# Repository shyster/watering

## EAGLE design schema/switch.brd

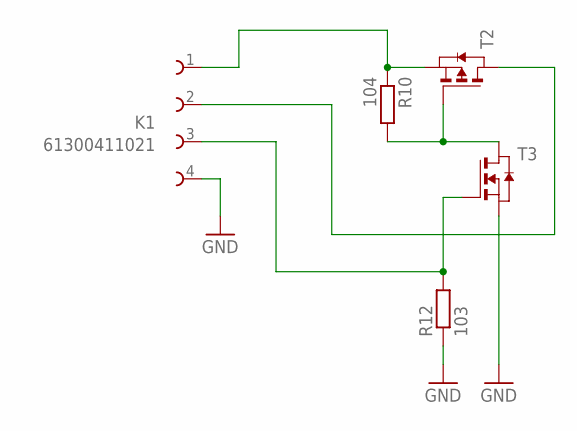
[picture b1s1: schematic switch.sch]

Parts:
K1: 61300411021
R10: 104; R0603
R12: 103; R0603
T2: PMOSSOT23; SOT-23
T3: NMOSSOT23; SOT-23

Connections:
GND: K1.4, R12.1, T3.2 (S)
unnamed: K1.2, T2.1 (D)
unnamed: R10.2, T2.3 (G), T3.1 (D)
unnamed: K1.3, R12.2, T3.3 (G)
unnamed: K1.1, R10.1, T2.2 (S)

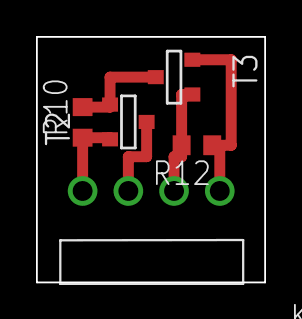
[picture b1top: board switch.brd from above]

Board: 2 copper layers, 12.7 x 13.6 mm, 5 parts (0 on the bottom side), 5 nets.

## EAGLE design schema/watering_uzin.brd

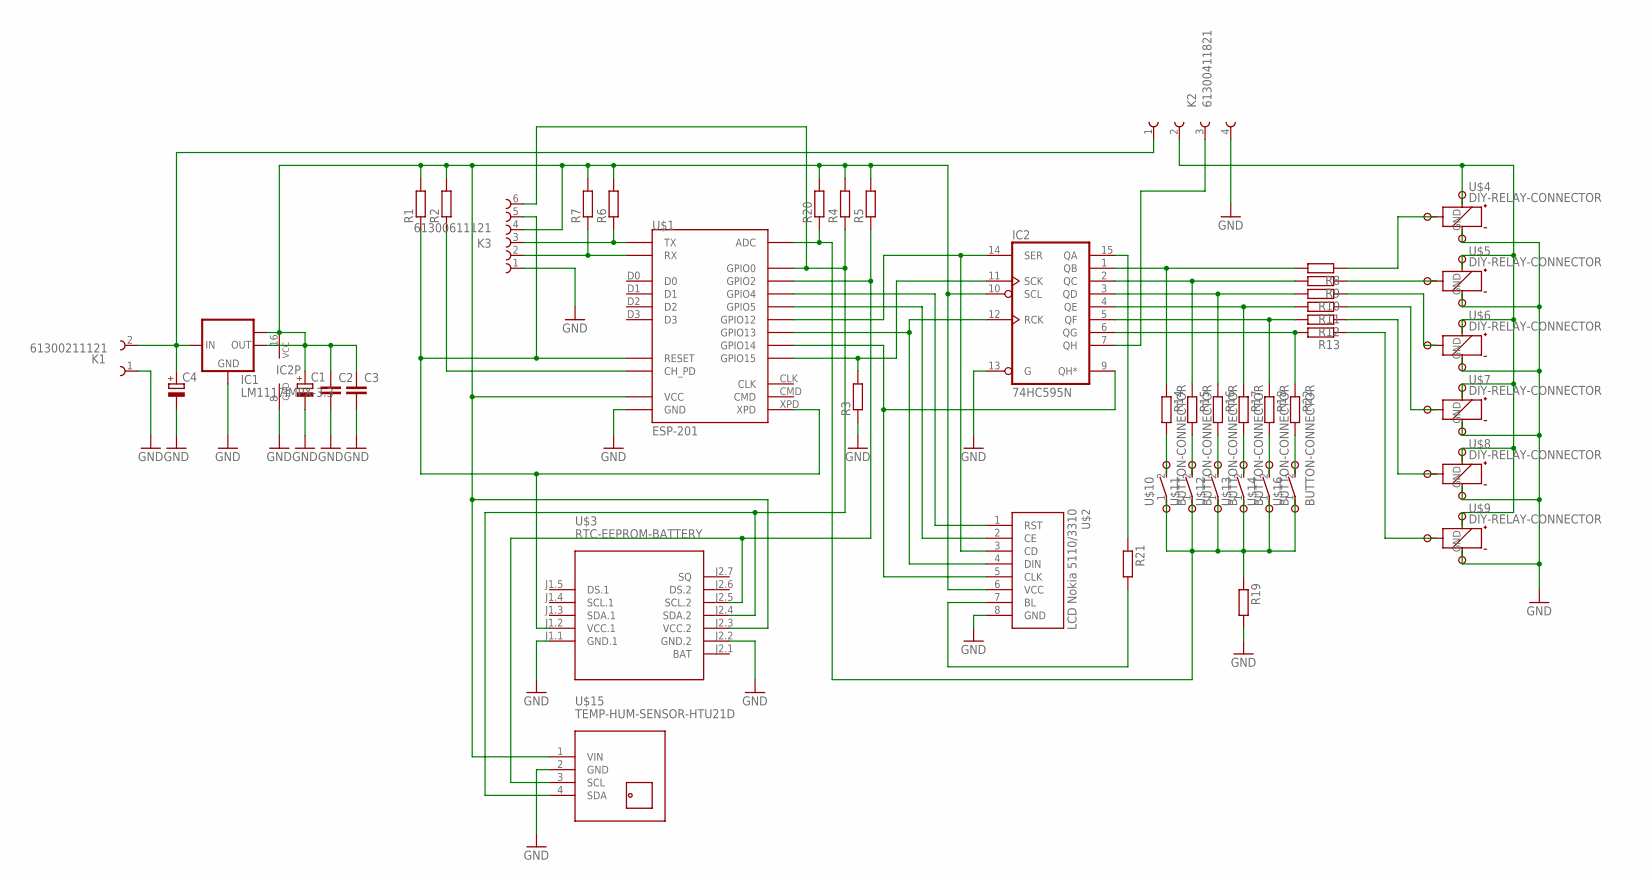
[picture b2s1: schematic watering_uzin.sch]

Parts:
C1, C4: CPOL-EUSANYO_F13; SANYO-OSCON_F13
C2, C3: C-EUC1210; C1210
IC1: LM1117IMPX-3.3; SOT223
IC2: 74HC595N; DIL16
K1: 61300211121
K2: 61300411821
K3: 61300611121
R1, R2, R3, R4, R5, R6, R7, R8, R9, R10, R11, R12, R13, R14, R15, R16, R17, R18, R19, R20, R21, R22: R-EU_R0805; R0805
U$1: ESP-201
U$2: NOKIA5110
U$3: RTC-EEPROM-BATTERY
U$4, U$5, U$6, U$7, U$8, U$9: DIY-RELAY-CONNECTOR
U$10, U$11, U$12, U$13, U$14, U$16: BUTTON-CONNECTOR
U$15: TEMP-HUM-SENSOR-HTU21D

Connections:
GND: C1.-, C2.2, C3.2, C4.-, IC1.1 (GND), IC2.8 (GND), IC2.13 (G), K1.1, K2.4, K3.1, R3.1, R19.2, U$1.GND, U$1.GND_2 (GND), U$1.GND_3 (GND), U$2.8 (GND), U$3.J1.1 (GND.1), U$3.J2.2 (GND.2), U$4.GND, U$5.GND, U$6.GND, U$7.GND, U$8.GND, U$9.GND, U$15.2 (GND)
unnamed: K3.5, R1.1, U$1.RST (RESET), U$1.XPD, U$3.J1.2 (VCC.1)
unnamed: R2.1, U$1.CH_PD
unnamed: R8.1, U$4.IN
unnamed: R9.1, U$5.IN
unnamed: R10.1, U$6.IN
unnamed: IC2.9 (QH*), U$1.GPIO14, U$2.5 (CLK)
unnamed: IC2.11 (SCK), R3.2, U$1.GPIO15
unnamed: K3.6, R4.1, U$1.GPIO0, U$3.J2.4 (SDA.2), U$15.4 (SDA)
unnamed: R5.1, U$1.GPIO2, U$3.J2.5 (SCL.2), U$15.3 (SCL)
unnamed: R19.1, R20.1, U$1.ADC, U$10.1, U$11.1, U$12.1, U$13.1, U$14.1, U$16.1
unnamed: K3.3, R6.1, U$1.TX
unnamed: IC2.14 (SER), U$1.GPIO12, U$2.3 (CD)
unnamed: IC2.12 (RCK), U$1.GPIO13, U$2.4 (DIN)
unnamed: R21.2, U$2.7 (BL)
unnamed: U$1.GPIO4, U$2.1 (RST)
unnamed: U$1.GPIO5, U$2.2 (CE)
unnamed: R11.1, U$7.IN
unnamed: R12.1, U$8.IN
unnamed: R13.1, U$9.IN
unnamed: K2.2, U$4.VCC, U$5.VCC, U$6.VCC, U$7.VCC, U$8.VCC, U$9.VCC
unnamed: IC2.1 (QB), R8.2, R14.1
unnamed: IC2.2 (QC), R9.2, R15.1
unnamed: IC2.3 (QD), R10.2, R16.1
unnamed: IC2.4 (QE), R11.2, R17.1
unnamed: IC2.5 (QF), R12.2, R18.1
unnamed: IC2.6 (QG), R13.2, R22.1
unnamed: R14.2, U$10.2 (S)
unnamed: R15.2, U$11.2 (S)
unnamed: R16.2, U$12.2 (S)
unnamed: R17.2, U$13.2 (S)
unnamed: R18.2, U$14.2 (S)
unnamed: C4.+, IC1.3 (IN), K1.2, K2.1
unnamed: IC2.7 (QH), K2.3
unnamed: K3.2, R7.1, U$1.RX
unnamed: R22.2, U$16.2 (S)
unnamed: IC2.15 (QA), R21.1
VCC: C1.+, C2.1, C3.1, IC1.2 (OUT), IC1.TAB (OUT1), IC2.10 (SCL), IC2.16 (VCC), K3.4, R1.2, R2.2, R4.2, R5.2, R6.2, R7.2, R20.2, U$1.3V3 (VCC), U$1.3V3_2 (VCC), U$1.3V3_3 (VCC), U$2.6 (VCC), U$3.J2.3 (VCC.2), U$15.1 (VIN)

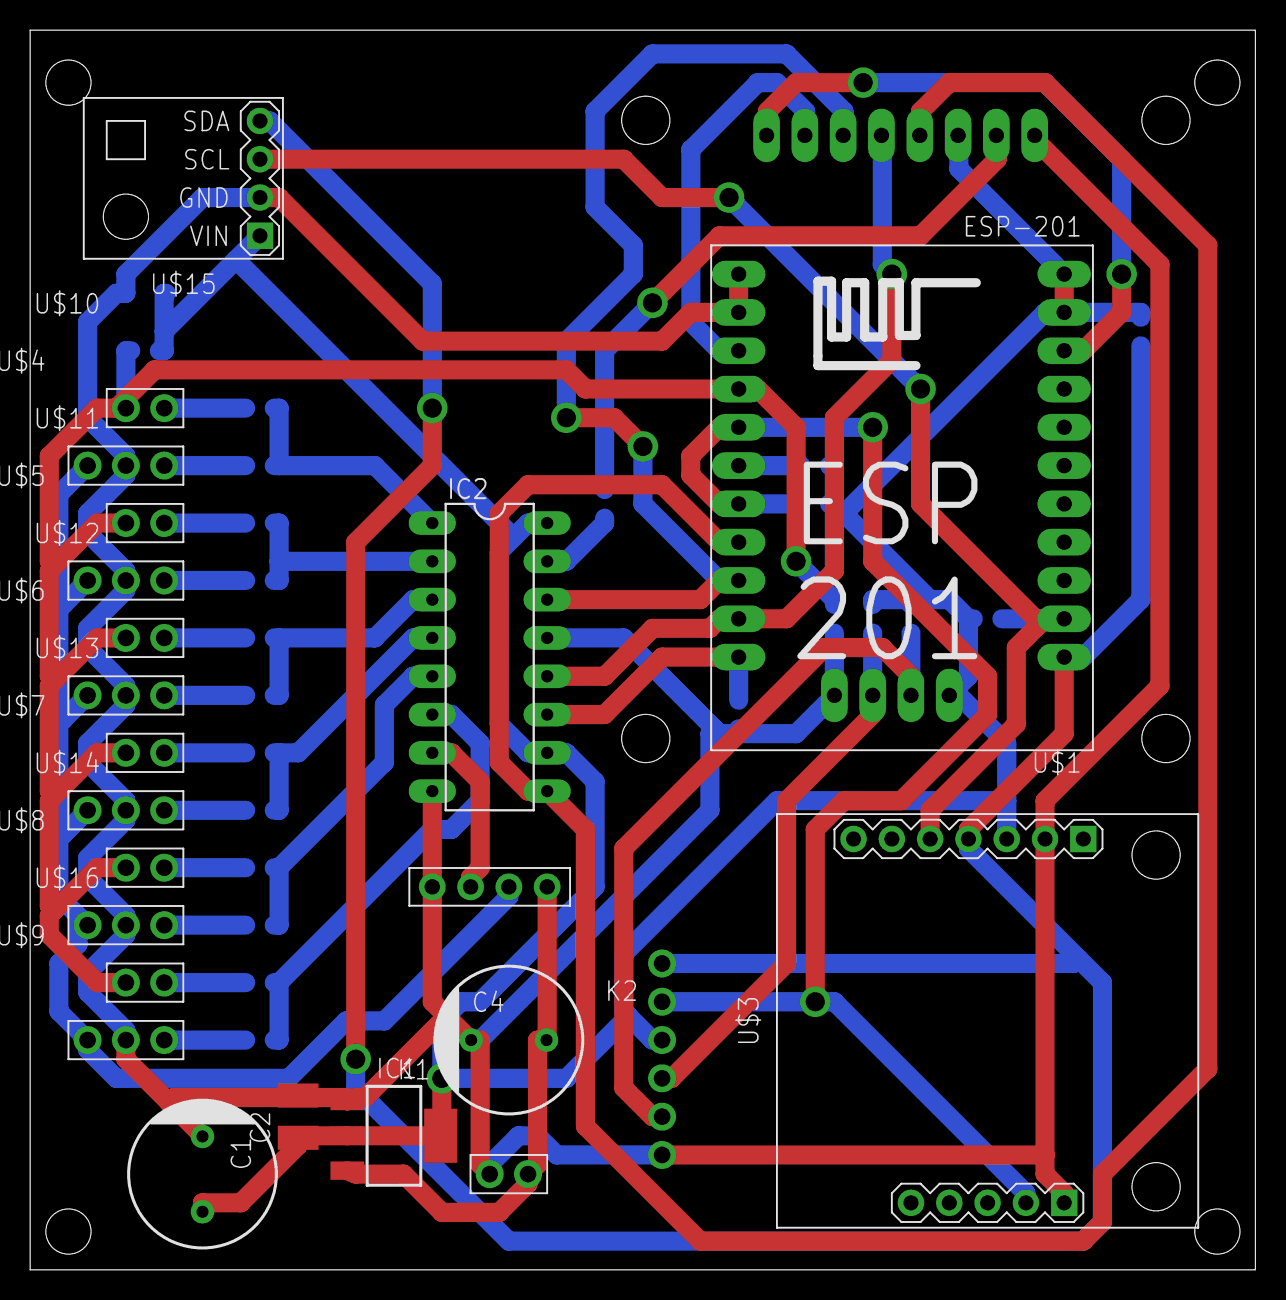
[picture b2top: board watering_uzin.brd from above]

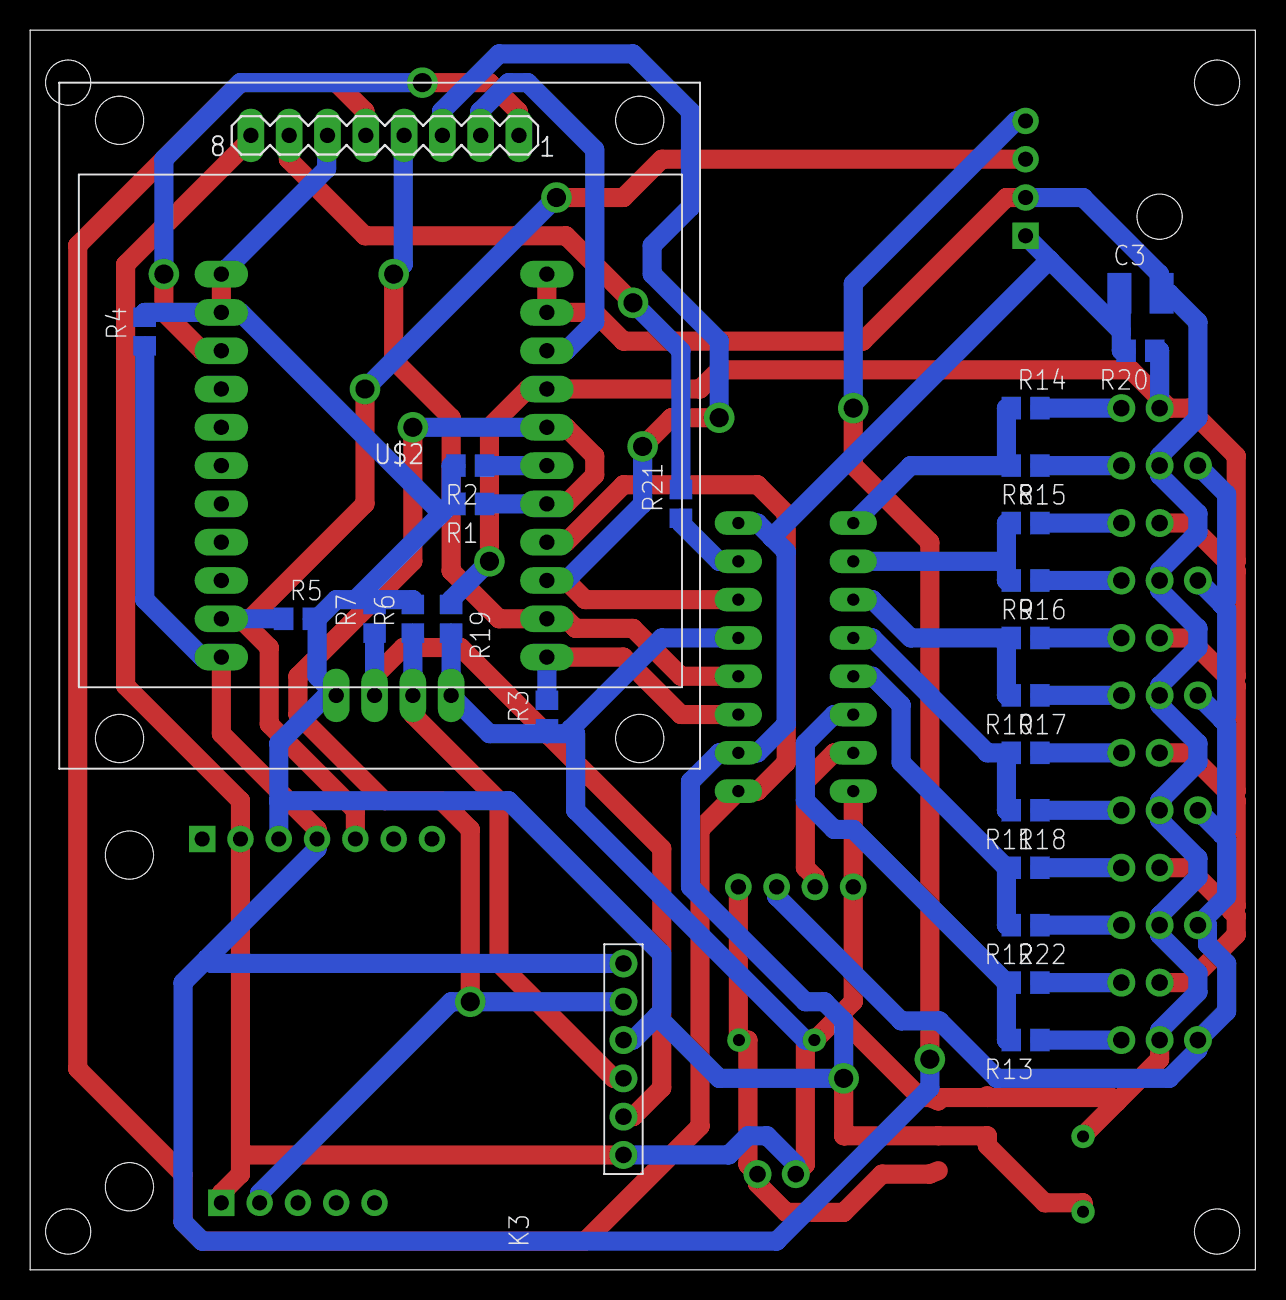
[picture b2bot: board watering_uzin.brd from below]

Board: 2 copper layers, 81.3 x 82.2 mm, 47 parts (25 on the bottom side), 38 nets.

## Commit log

2017-10-11 Add files

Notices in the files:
parts and their libraries:
Board_to_Board_Connectors_rev15d: Copyright: Würth Elektronik
diy-modules: Released under the Creative Commons Attribution 4.0 International License: http://creativecommons.org/licenses/by/4.0
